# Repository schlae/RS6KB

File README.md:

# RS6KB - Use PS/2 Keyboards with RS/6000s
Old RS/6000 computers don't fully support PS/2 keyboards. They were originally designed to use a Model M keyboard with lightly modified firmware and a speaker. (Ever wonder what the speaker grille is for inside such a keyboard?)

The firmware change implements a single new command, 0xEF. This queries the keyboard to find out if it uses a standard 101 key layout or the "world trade" 102 key layout. Unfortunately, if the computer doesn't receive a response to this command, it generates a keyboard error and won't boot into service mode correctly. The firmware in this project is hard coded to the US 101 key layout but by changing the response byte 0xB0 to 0xB1 it can be made to work with the 102 key "world trade" (ISO) layout.

| Host | Keyboard | Keyboard | Keyboard |
| ---- | -------- | -------- | -------- |
| 0xEF (Layout ID) | 0xFA (Ack) | 0xB0 (US 101 key) or 0xB1 (WT 102 key) | 0xBF |

For technical details of the protocol, see page 356 of the [RS/6000 Hardware Technical Reference General Information](http://bitsavers.org/pdf/ibm/rs6000/SA23-2643-00_RS6000_Hardware_Technical_Reference_General_Information_1990.pdf) manual.

This project corrects the issue by snooping the PS/2 bus. It watches for the 0xEF command, and when that comes through, it disconnects the keyboard, generates the correct response to the command, and then reconnects the keyboard.

The hardware is a small circuit board with a microcontroller and connectors to allow you to plug in the keyboard and a short wire with a plug going to the host RS/6000 machine.

## Fabrication

The board dimensions are 34mm x 24mm. It is a simple two-layer board. If you're in the USA, it's pretty easy and cheap to get it from [Osh Park](https://oshpark.com). Or just toss it in with your next big order from one of the other PCB vendors.

[Schematic](https://github.com/schlae/RS6KB/blob/main/RS6KB.pdf)

[Fab files](https://github.com/schlae/RS6KB/blob/main/fab/RS6KB_Rev1.zip)

[Bill of Materials](https://github.com/schlae/RS6KB/blob/main/RS6KB.csv)

## Assembly

Put down the surface mount components first. I'd recommend installing the programming connector, J3, but don't install the remaining through-hole components until you've successfully programmed the bootloader. Otherwise those parts might get in the way of any solder cleanup work you might need to perform.

The project uses an ATMega328P with the Arduino bootloader, so you'll need to program that next. There are a couple of options, but I've used the Arduino-As-ISP sketch in another Arduino (but be aware that you need to connect a [10uF capacitor between the RST pin on the Arduino and ground](https://forum.arduino.cc/t/arduinoisp-on-uno-requires-10uf-cap-why/102111) for it to work correctly). You can also use something like a USBtinyISP ([AVR Pocket Programmer](https://www.sparkfun.com/products/9825)). Newer versions of the Arduino IDE seem to have an issue programming the lock bits. I used an older version (1.8.16) which worked fine. Program the board as an Arduino Nano or as an Arduino Pro Mini (16MHz).

Once that is done, attach a 6-pin serial adapter such as the [SparkFun FTDI Basic (**5V version**)](https://www.sparkfun.com/products/9716), load the RS6KB.ino sketch, and make sure it downloads correctly.

Then go ahead and install the remaining through-hole parts.

## The Keyboard Cable

Header J2 connects to the RS/6000 through a cable. One end is a 6-pin header, and the other end is a male 6-pin Mini-DIN plug. The pins are connected 1:1 (pin 1 to pin 1, and so on). You could get an in-line Mini-DIN plug and solder it to a short length of wire, or you could sacrifice an old keyboard cable.

It is up to you if you want to solder the wires on the cable directly to the footprint or install a header and connector combination.

Pins 2 and 6 are brought out to header J5 for an optional clicky speaker.

The pinout is reproduced here for reference. It is also inscribed in silkscreen on the back of the board for convenience.

| Pin | Signal         |
| --- | -------------- |
| 1   | Keyboard data  |
| 2   | Speaker signal |
| 3   | Ground         |
| 4   | +5V            |
| 5   | Keyboard clock |
| 6   | Speaker ground |

## Other Notes

I've only tested this with an RS/6000 model 7006 and a genuine IBM Model M keyboard, so I wouldn't be surprised if other keyboards don't work properly. Since I'm not a keyboard collector, I won't be able to help you because it's very unlikely I'll have your exact keyboard, but if you have a USB logic analyzer, you could try doing a little troubleshooting to see where the firmware is getting hung up.

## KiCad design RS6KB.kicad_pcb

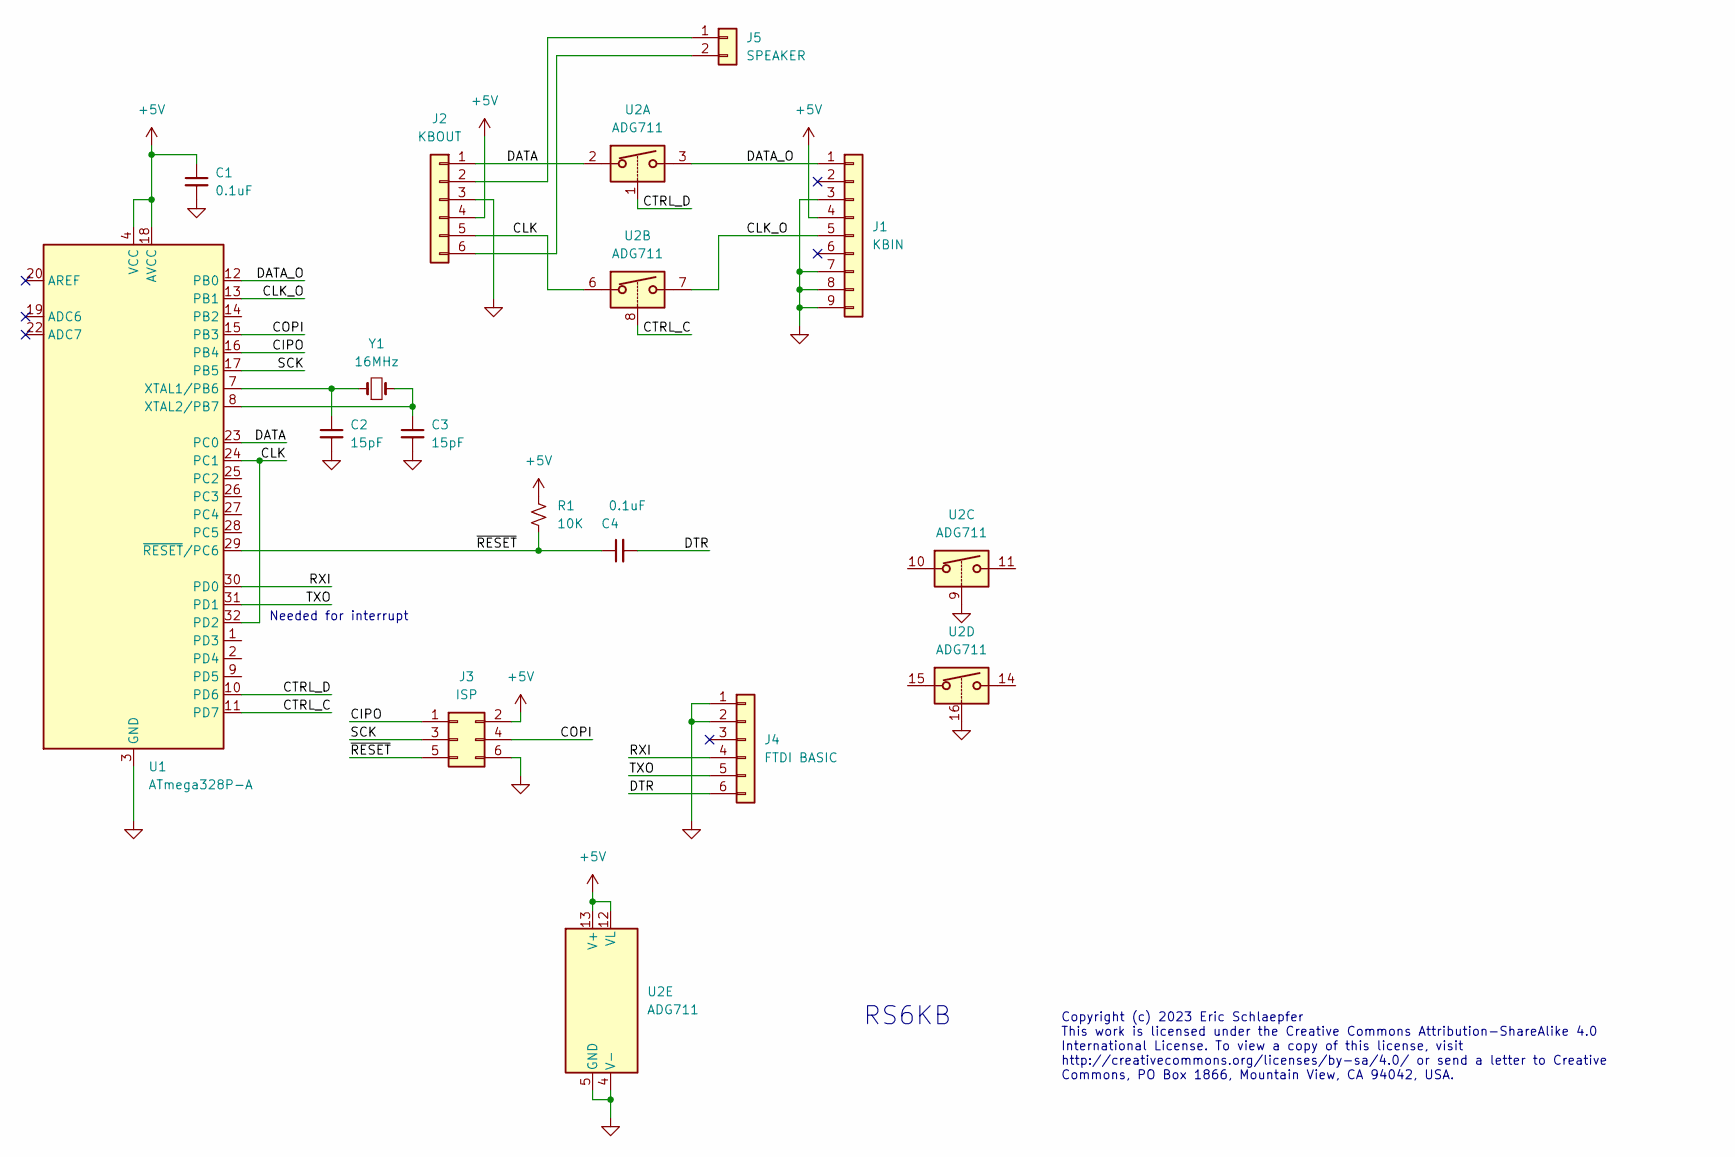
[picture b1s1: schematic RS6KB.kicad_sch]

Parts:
C1, C4: 0.1uF; CAPC1608X100
C2, C3: 15pF; CAPC1608X100
J1: KBIN; CUI_MD-60SG; Mouser 806-KMDGX-6S-BS
J2: KBOUT; PinHeader_1x06_P2.54mm_Vertical
J3: ISP; PinHeader_2x03_P2.54mm_Vertical
J4: FTDI BASIC; PinHeader_1x06_P2.54mm_Vertical
J5: SPEAKER; PinHeader_1x02_P2.54mm_Vertical
R1: 10K; RESC1608X55
U1: ATmega328P-A; TQFP80P900X900X120-32
U2: ADG711; TSOP65P640X110-16; Mouser 584-ADG711BRUZ-R7
Y1: 16MHz; XTAL500X320X120-2; Mouser 815-ABM3-16-B2-T

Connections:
+5V: C1.1, J1.4, J2.4, J3.2, R1.1, U1.4 (VCC), U1.6 (VCC), U1.18 (AVCC), U2.12 (VL), U2.13 (V+)
/CIPO: J3.1, U1.16 (PB4)
/CLK: J2.5, U1.24 (PC1), U1.32 (PD2), U2.6
/CLK_O: J1.5, U1.13 (PB1), U2.7
/COPI: J3.4, U1.15 (PB3)
/CTRL_C: U1.11 (PD7), U2.8
/CTRL_D: U1.10 (PD6), U2.1
/DATA: J2.1, U1.23 (PC0), U2.2
/DATA_O: J1.1, U1.12 (PB0), U2.3
/DTR: C4.2, J4.6
/RXI: J4.4, U1.30 (PD0)
/SCK: J3.3, U1.17 (PB5)
/TXO: J4.5, U1.31 (PD1)
/~RESET: C4.1, J3.5, R1.2, U1.29 (~RESET/PC6)
GND: C1.2, C2.2, C3.2, J1.3, J1.7, J1.8, J1.9, J2.3, J3.6, J4.1, J4.2, U1.3 (GND), U1.5 (GND), U1.21 (GND), U2.4 (V-), U2.5 (GND), U2.9, U2.16
unnamed: C2.1, U1.7 (XTAL1/PB6), Y1.1
unnamed: C3.1, U1.8 (XTAL2/PB7), Y1.2
unnamed: J2.2, J5.1
unnamed: J2.6, J5.2

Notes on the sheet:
Copyright (c) 2023 Eric Schlaepfer This work is licensed under the Creative Commons Attribution-ShareAlike 4.0 International License. To view a copy of this license, visit http://creativecommons.org/licenses/by-sa/4.0/ or send a letter to Creative Commons, PO Box 1866, Mountain View, CA 94042, USA.
RS6KB
Needed for interrupt

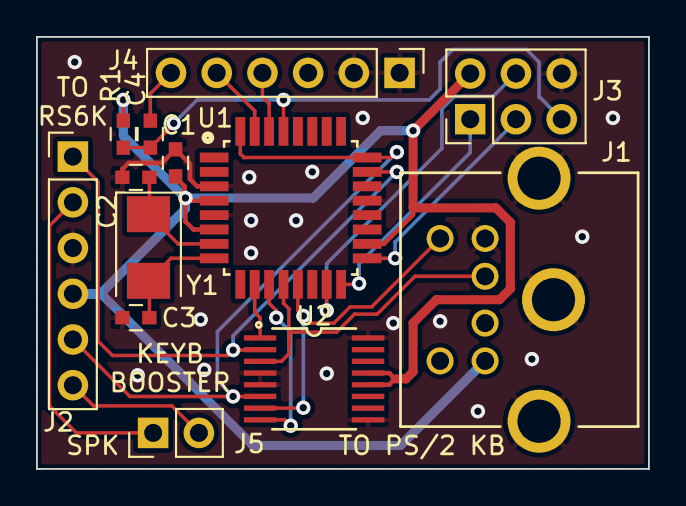
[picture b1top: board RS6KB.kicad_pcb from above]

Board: 2 copper layers, 34.0 x 24.0 mm, 13 parts (0 on the bottom side), 19 nets.

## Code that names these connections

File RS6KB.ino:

// RS6KB
//
// Copyright (c) 2023 Eric Schlaepfer
// This work is licensed under the Creative Commons Attribution-ShareAlike 4.0
// International License. To view a copy of this license, visit
// http://creativecommons.org/licenses/by-sa/4.0/ or send a letter to Creative
// Commons, PO Box 1866, Mountain View, CA 94042, USA.

#include <avr/io.h>
#include <util/delay.h>
#include <stdint.h>
#include <avr/interrupt.h>

// IO pin assignments
// PB0 = PS/2 data (keyboard side)
// PB1 = PS/2 clock (keyboard side)
// PC0 = PS/2 data (RS/6000 side)
// PC1 = PS/2 clock (RS/6000 side)
// PD2 = Tied to PC1, used as edge-triggered interrupt input
// PD6 = Analog switch control data line
// PD7 = Analog switch control clock line

#define TIMEOUT (200)

#define STATE_IDLE (0)
#define STATE_XFER_HOST (1)
#define STATE_XFER_KEYB (2)

#define BIT_COUNT_HOST (12)
#define BIT_COUNT_KEYB (10)

volatile uint8_t state = STATE_IDLE;
uint8_t dbcount;
uint16_t data_shift;
volatile uint16_t data_out;
volatile bool data_ready = false;
volatile bool host = false;

volatile int timeout = 0;

inline void SetIntFalling()
{
  EICRA = _BV(ISC01);
}

inline void SetIntRising()
{
  EICRA = _BV(ISC00) | _BV(ISC01); 
}

inline void KeyDisconnect()
{
  PORTD |= 0xC0;
}

inline void KeyConnect()
{
  PORTD &= ~0xC0;
}

void setup() {
  // put your setup code here, to run once:
  Serial.begin(115200);

  DDRB = 0x00; // All inputs
  DDRC = 0x00; // All inputs
  DDRD = 0xC0 | _BV(3); // Control are outputs. Normally open
  PORTD = 0;
  KeyConnect(); // Set the switches on.

  // Configure PD2 as an interrupt, falling edge.
  EICRA = _BV(ISC01); 
  EIMSK = _BV(INT0);
  state = STATE_IDLE;
  sei();
  Serial.println("Begin.");
}

// Computes the parity bit for the PS/2 protocol
int CalcParity(uint16_t by)
{
  uint16_t i, sum = 0;
  for (i = 0; i < 8; i++) {
    sum += ((by >> i) & 1);
  }
  return (~sum & 1);
}

// Transmits a byte to the RS/6K side. Generates clocks
void SendByte(uint16_t by)
{
  int i;
  by |= (CalcParity(by) << 8) | 0xE00;
  DDRC = 0x1; // Start bit
  for (i = 0; i < 10; i++) {
    delayMicroseconds(20);
    DDRC |= 0x2; // Clock goes low
    delayMicroseconds(40);
    DDRC &= 0x1; // Clock goes high
    delayMicroseconds(20);
    DDRC = (~by >> i) & 1; // Set the new bit
  }
  delayMicroseconds(20);
  DDRC = 0x2; // Clock low, data high
  delayMicroseconds(75); // Wait for ack?
  DDRC = 0x0; // Clock high
  // Done
}

// Main state machine
SIGNAL(INT0_vect)
{
  uint8_t d = PINC & 0x1;

  #ifdef DEBUGGING
  PORTD |= _BV(3);
  PORTD &= ~_BV(3);
  #endif

  timeout = 0;
  switch(state) {
    case STATE_IDLE:
      if (d == 1) {
        state = STATE_XFER_HOST; // Host mode transfer
        SetIntRising(); // On a host mode transfer we look at the rising edges
        dbcount = 0;
        data_shift = 0;
      } else {
        state = STATE_XFER_KEYB; // Keyboard mode transfer
        dbcount = 0;
        data_shift = 0;
      }
      break;
    case STATE_XFER_HOST: // Host mode data bit transfer
      data_shift |= d << dbcount++; // Clock it in
      if (dbcount == BIT_COUNT_HOST) {
        // Shift it to drop start bit
        data_out = data_shift >> 1;
        host = true;
        data_ready = true;
        SetIntFalling();
        state = STATE_IDLE;
      }
      break;
    case STATE_XFER_KEYB: // Keyboard mode data bit transfer
      data_shift |= d << dbcount++; // Clock it in
      if (dbcount == BIT_COUNT_KEYB) {
        data_out = data_shift; // No start bit, that's the first edge that we already caught.
        host = false;
        data_ready = true;
        state = STATE_IDLE;
      }
      break;
    default:
      SetIntFalling();
      state = STATE_IDLE;
  }
}

// Check for the host to send the EF command
// then generate the magic response code
void ListenByte()
{
  if (data_ready) { // Wait for a data byte
    data_ready = false;
    if (host && ((data_out & 0xFF) == 0xEF)) { // The magical mystery command: 0xEF is Layout ID
      cli();
      KeyDisconnect();
      delayMicroseconds(600);
      SendByte(0xFA); // Acknowledge the command
      delayMicroseconds(400);
      SendByte(0xB0); // B0 = United States 101 key layout. (B1 is the World Trade 102 key layout)
      delayMicroseconds(400);
      SendByte(0xBF); // BF is a byte common to both layouts.
      KeyConnect(); // And we are done. Whew!
      state = STATE_IDLE;
      SetIntFalling();
      sei();
    }

  }
}

// Reset state machine if the clock stays low for too low
void DoClockLowTimeout()
{
  if (!(PINC & 0x2)) {
    timeout = 0;
  } else {
    if (timeout++ > TIMEOUT) {
      cli();
      PORTD |= _BV(3);
      delayMicroseconds(10);
      PORTD &= ~_BV(3);
      timeout = 0;
      SetIntFalling();
      state = STATE_IDLE;
      sei();
    }
  }
}

void loop() {
  ListenByte();
  DoClockLowTimeout();
}

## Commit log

2023-07-29 Added some links and details

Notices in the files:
RS6KB.kicad_pcb:
Copyright (c) 2023 Tube Time. This work is licensed under the Creative Commons
©2023 Tube Time
